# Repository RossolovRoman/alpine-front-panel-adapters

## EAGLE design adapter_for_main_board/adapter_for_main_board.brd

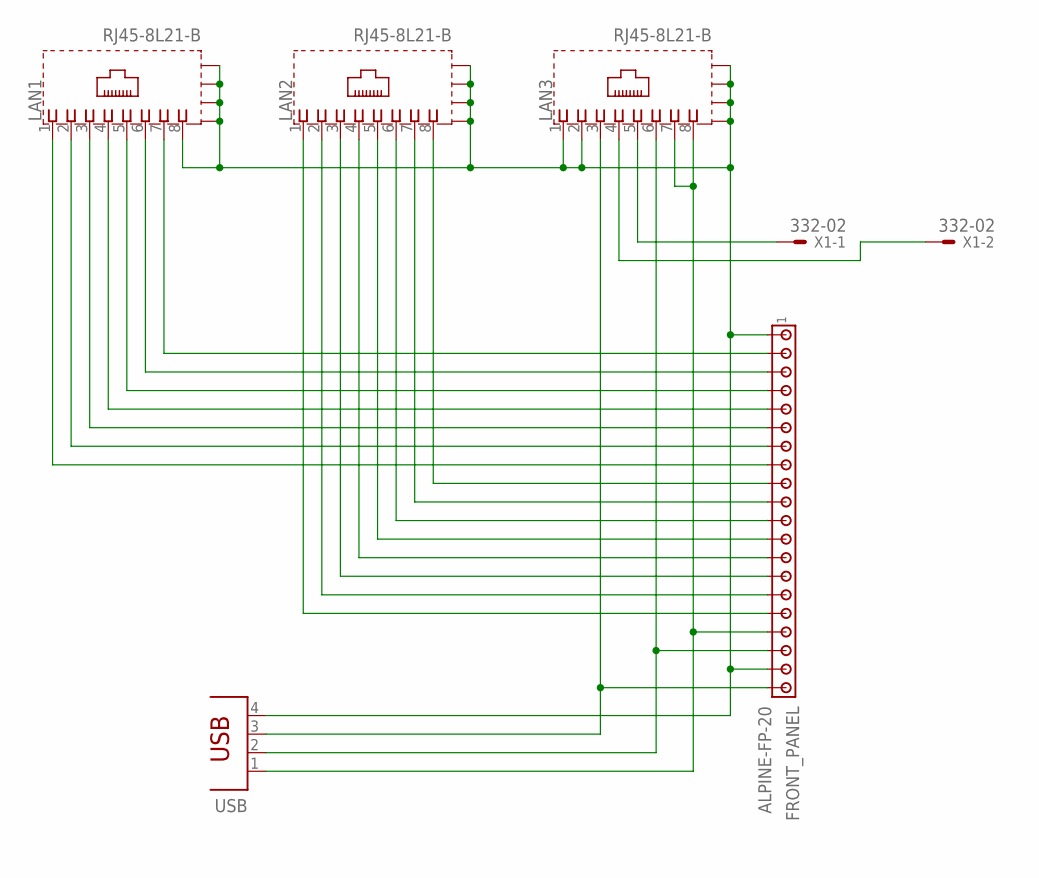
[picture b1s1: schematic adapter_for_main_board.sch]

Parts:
FRONT_PANEL: ALPINE-FP-20
LAN1, LAN2, LAN3: RJ45-8L21-B; RJ45-SHIELD1
USB: PN87520
X1: 332-02

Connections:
GND: FRONT_PANEL.1, FRONT_PANEL.19, LAN1.8, LAN1.S1 (S), LAN1.S2 (S), LAN1.S3 (S), LAN1.S4 (S), LAN2.S1 (S), LAN2.S2 (S), LAN2.S3 (S), LAN2.S4 (S), LAN3.1, LAN3.2, LAN3.S1 (S), LAN3.S2 (S), LAN3.S3 (S), LAN3.S4 (S), USB.4
unnamed: FRONT_PANEL.17, LAN3.7, LAN3.8, USB.1
unnamed: FRONT_PANEL.18, LAN3.6, USB.2
unnamed: FRONT_PANEL.20, LAN3.3, USB.3
unnamed: FRONT_PANEL.2, LAN1.7
unnamed: FRONT_PANEL.3, LAN1.6
unnamed: FRONT_PANEL.4, LAN1.5
unnamed: FRONT_PANEL.5, LAN1.4
unnamed: FRONT_PANEL.6, LAN1.3
unnamed: FRONT_PANEL.7, LAN1.2
unnamed: FRONT_PANEL.8, LAN1.1
unnamed: FRONT_PANEL.9, LAN2.8
unnamed: FRONT_PANEL.10, LAN2.7
unnamed: FRONT_PANEL.11, LAN2.6
unnamed: FRONT_PANEL.12, LAN2.5
unnamed: FRONT_PANEL.13, LAN2.4
unnamed: FRONT_PANEL.14, LAN2.3
unnamed: FRONT_PANEL.15, LAN2.2
unnamed: FRONT_PANEL.16, LAN2.1
unnamed: LAN3.5, X1.1
unnamed: LAN3.4, X1.2

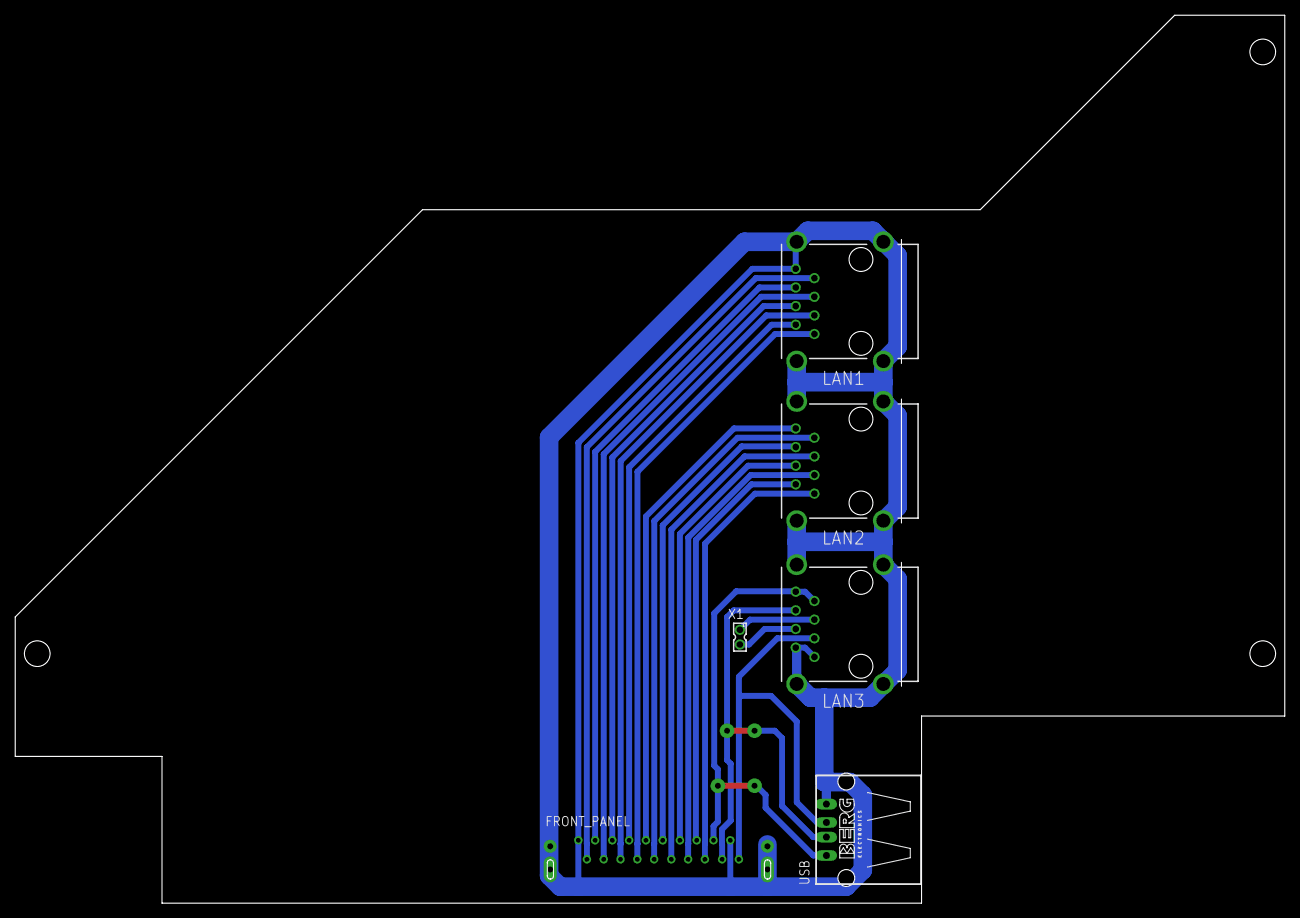
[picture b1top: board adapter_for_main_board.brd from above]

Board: 2 copper layers, 173.0 x 121.0 mm, 6 parts (0 on the bottom side), 21 nets.

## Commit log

2021-07-18 Add library for Alpine with front panel connector
2021-07-18 Add custom main board
2021-07-18 Add adapter for original main board
